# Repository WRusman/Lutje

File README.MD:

Open-source Battlebot ELRS receiver with built-in ESC's' for 2 brushed driving motors, 1 brushed weapon motor and 2 PWM outputs for external ESC.

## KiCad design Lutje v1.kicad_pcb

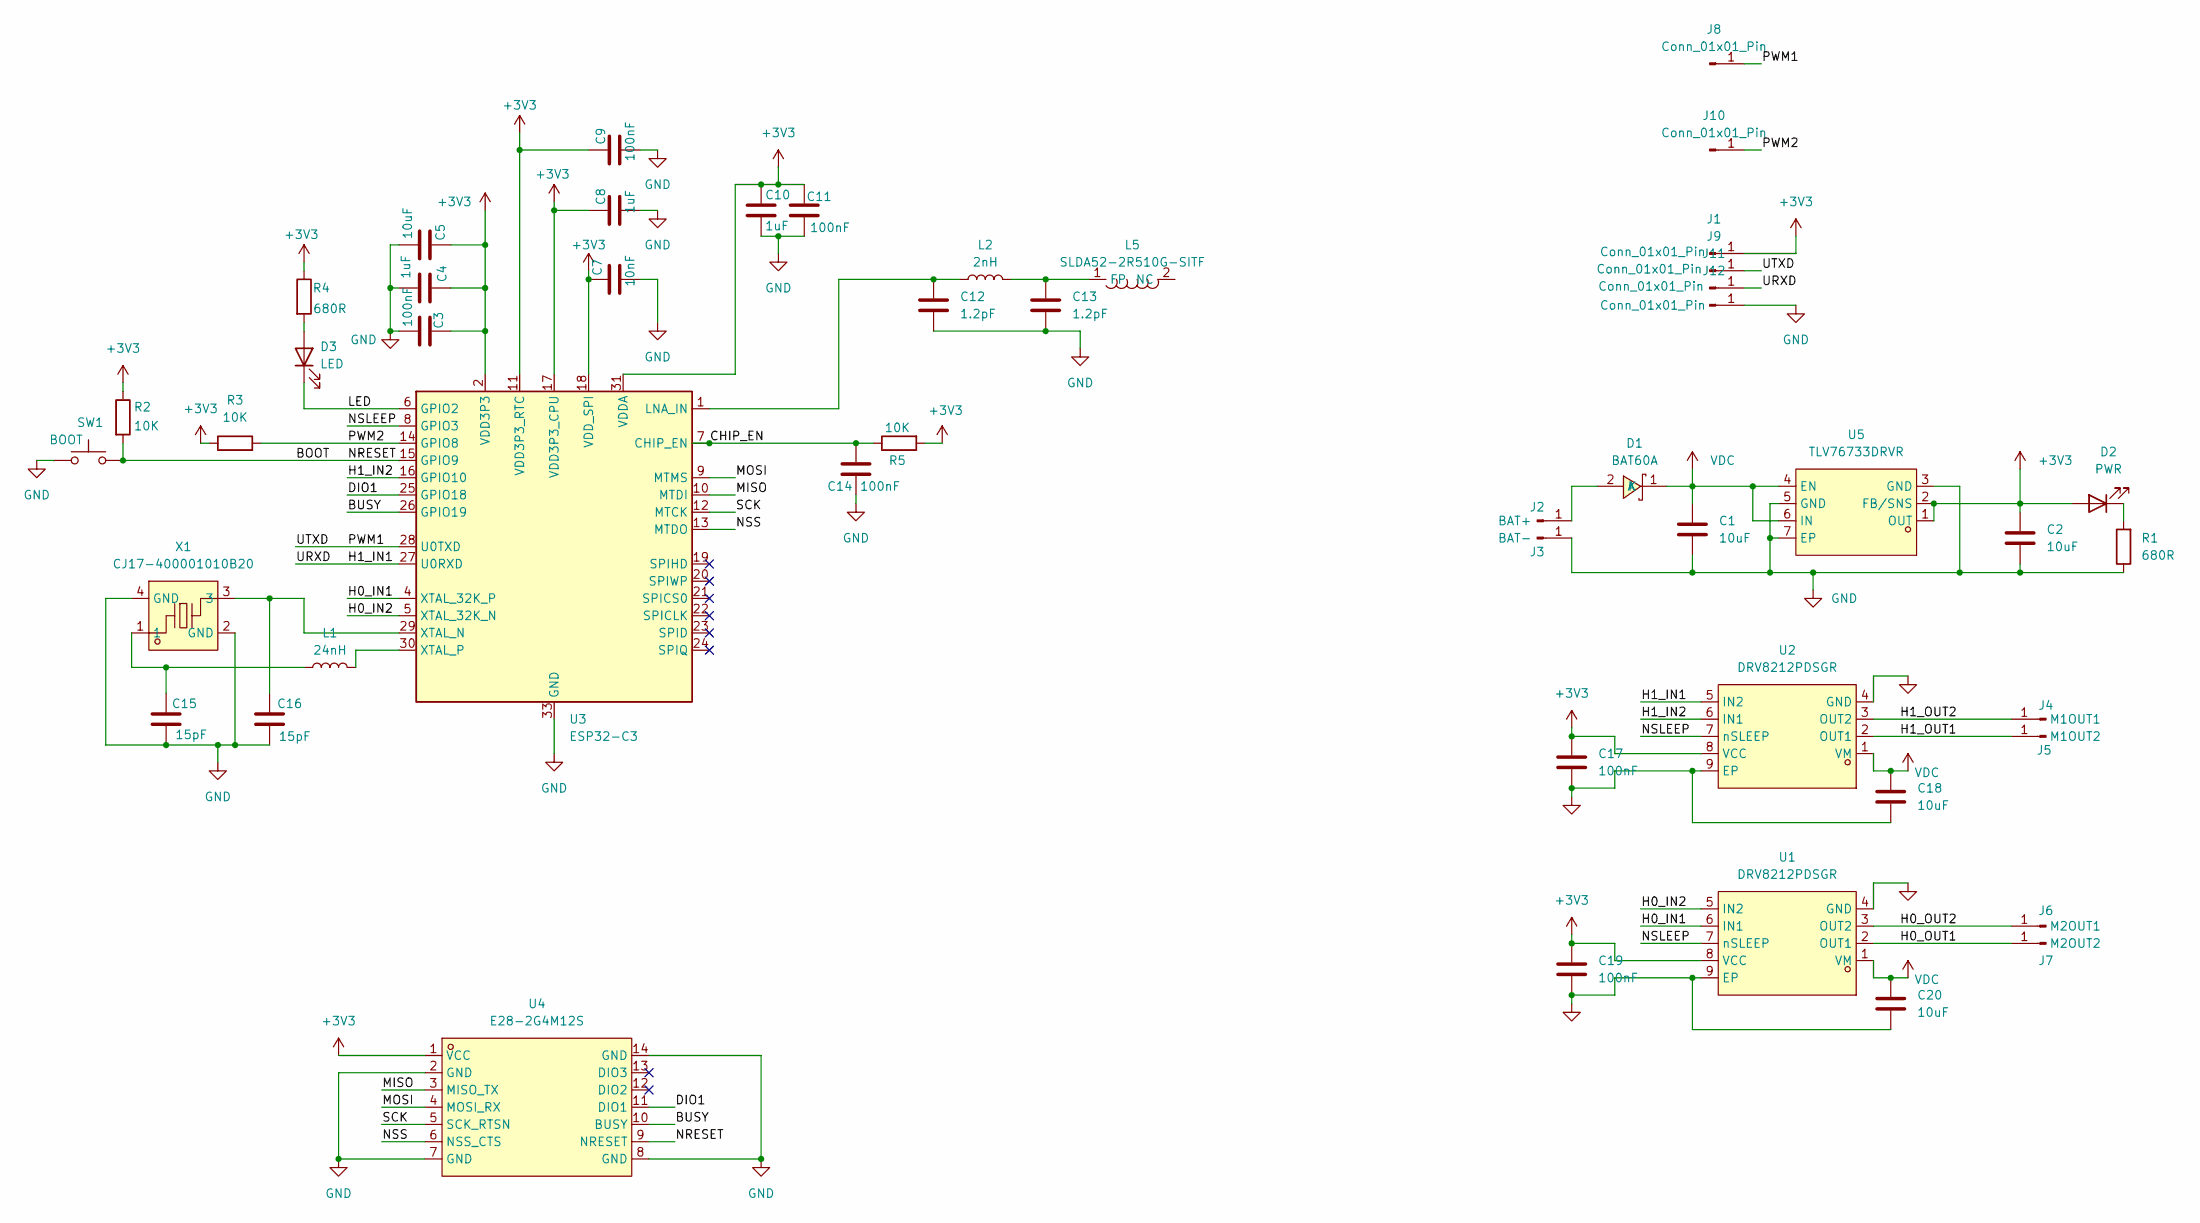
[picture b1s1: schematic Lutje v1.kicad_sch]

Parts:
C1, C2, C5, C18, C20: 10uF; C_0201_0603Metric; LCSC C96446
C3, C9, C11, C14, C17, C19: 100nF; C_0201_0603Metric; LCSC C14663
C4, C8, C10: 1uF; C_0201_0603Metric; LCSC C15849
C7: 10nF; C_0201_0603Metric; LCSC C57112
C12, C13: 1.2pF; C_0201_0603Metric; LCSC C1638
C15, C16: 15pF; C_0201_0603Metric; LCSC C1644
D1: BAT60A; SOD-323_L1.8-W1.3-LS2.5-RD; MPN BAT60A; LCSC Part C5355496
D2: PWR; LED_0201_0603Metric; LCSC C2286
D3: LED; LED_0201_0603Metric; LCSC C2286
J1, J9, J11, J12: Conn_01x01_Pin; SolderWirePad_1x01_SMD_1x2mm
J2: BAT+; SolderWirePad_1x01_SMD_1.5x3mm
J3: BAT-; SolderWirePad_1x01_SMD_1.5x3mm
J4: M1OUT1; SolderWirePad_1x01_SMD_1.5x3mm
J5: M1OUT2; SolderWirePad_1x01_SMD_1.5x3mm
J6: M2OUT1; SolderWirePad_1x01_SMD_1.5x3mm
J7: M2OUT2; SolderWirePad_1x01_SMD_1.5x3mm
J8, J10: Conn_01x01_Pin; SolderWirePad_1x01_SMD_1.5x3mm
L1: 24nH; L_0201_0603Metric; LCSC C74305
L2: 2nH; L_0201_0603Metric; LCSC C1028
L5: SLDA52-2R510G-SITF; ANT-SMD_L5.2-W2.1; MPN SLDA52-2R510G-S1TF; LCSC Part C96745
R1, R4: 680R; R_0201_0603Metric; LCSC C23228
R2, R3, R5: 10K; R_0201_0603Metric; LCSC C25804
SW1: BOOT; SW_Push_SPST_NO_Alps_SKRK; LCSC Part C202388
U1, U2: DRV8212PDSGR; WSON-8_L2.0-W2.0-P0.50-TL-EP; MPN DRV8212PDSGR; LCSC Part C5208051
U3: ESP32-C3; QFN-32-1EP_5x5mm_P0.5mm_EP3.7x3.7mm; LCSC Part C2858491
U4: E28-2G4M12S; WIRELM-SMD_E28-2G4M12S; MPN E28-2G4M12S; LCSC Part C411310
U5: TLV76733DRVR; WSON-6_L2.0-W2.0-P0.65-TL-EP; MPN TLV76733DRVR; LCSC Part C2848334
X1: CJ17-400001010B20; CRYSTAL-SMD_4P-L1.6-W1.2-BL; MPN CJ17-400001010B20; LCSC Part C2875272

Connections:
+3V3: C2.1, C3.2, C4.2, C5.2, C7.1, C8.1, C9.1, C10.1, C11.1, C17.1, C19.1, D2.2 (A), J1.1 (Pin_1_1), R2.1, R3.1, R4.1, R5.2, U1.8 (VCC), U2.8 (VCC), U3.2 (VDD3P3), U3.3 (VDD3P3), U3.11 (VDD3P3_RTC), U3.17 (VDD3P3_CPU), U3.18 (VDD_SPI), U3.31 (VDDA), U3.32 (VDDA), U4.1 (VCC), U5.1 (OUT), U5.2 (FB/SNS)
/BOOT: R2.2, SW1.2, U3.15 (GPIO9), U4.9 (NRESET)
/BUSY: U3.26 (GPIO19), U4.10 (BUSY)
/CHIP_EN: C14.1, R5.1, U3.7 (CHIP_EN)
/DIO1: U3.25 (GPIO18), U4.11 (DIO1)
/H0_IN1: U1.6 (IN1), U3.4 (XTAL_32K_P)
/H0_IN2: U1.5 (IN2), U3.5 (XTAL_32K_N)
/H0_OUT1: J7.1 (Pin_1_1), U1.2 (OUT1)
/H0_OUT2: J6.1 (Pin_1_1), U1.3 (OUT2)
/H1_IN1: J11.1 (Pin_1_1), U2.5 (IN2), U3.27 (U0RXD)
/H1_IN2: U2.6 (IN1), U3.16 (GPIO10)
/H1_OUT1: J5.1 (Pin_1_1), U2.2 (OUT1)
/H1_OUT2: J4.1 (Pin_1_1), U2.3 (OUT2)
/LED: D3.1 (K), U3.6 (GPIO2)
/MISO: U3.10 (MTDI), U4.3 (MISO_TX)
/MOSI: U3.9 (MTMS), U4.4 (MOSI_RX)
/NSLEEP: U1.7 (nSLEEP), U2.7 (nSLEEP), U3.8 (GPIO3)
/NSS: U3.13 (MTDO), U4.6 (NSS_CTS)
/PWM1: J8.1 (Pin_1_1), J9.1 (Pin_1_1), U3.28 (U0TXD)
/PWM2: J10.1 (Pin_1_1), R3.2, U3.14 (GPIO8)
/SCK: U3.12 (MTCK), U4.5 (SCK_RTSN)
GND: C1.2, C2.2, C3.1, C4.1, C5.1, C7.2, C8.2, C9.2, C10.2, C11.2, C12.2, C13.2, C14.2, C15.2, C16.2, C17.2, C18.2, C19.2, C20.2, J3.1 (Pin_1_1), J12.1 (Pin_1_1), R1.1, SW1.1, U1.4 (GND), U1.9 (EP), U2.4 (GND), U2.9 (EP), U3.33 (GND), U4.2 (GND), U4.7 (GND), U4.8 (GND), U4.14 (GND), U5.3 (GND), U5.5 (GND), U5.7 (EP), X1.2 (GND), X1.4 (GND)
unnamed: C15.1, L1.1, X1.1
unnamed: D1.2 (A), J2.1 (Pin_1_1)
unnamed: D2.1 (K), R1.2
unnamed: D3.2 (A), R4.2
unnamed: C13.1, L2.2, L5.1 (FP_1)
unnamed: C12.1, L2.1, U3.1 (LNA_IN)
unnamed: C16.1, U3.29 (XTAL_N), X1.3
unnamed: L1.2, U3.30 (XTAL_P)
VDC: C1.1, C18.1, C20.1, D1.1 (K), U1.1 (VM), U2.1 (VM), U5.4 (EN), U5.6 (IN)

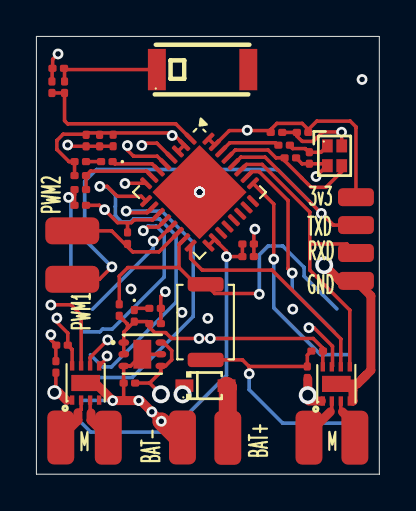
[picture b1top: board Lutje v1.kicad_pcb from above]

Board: 4 copper layers, 19.0 x 24.3 mm, 49 parts (1 on the bottom side), 31 nets.

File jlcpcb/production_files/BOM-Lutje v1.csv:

Comment,Designator,Footprint,LCSC,Quantity
1.2pF,"C12,C13",C_0201_0603Metric,C1638,2
100nF,"C11,C14,C17,C19,C3,C9",C_0201_0603Metric,C14663,6
10K,"R2,R3,R5",R_0201_0603Metric,C25804,3
10nF,C7,C_0201_0603Metric,C57112,1
10uF,"C1,C18,C2,C20,C5",C_0201_0603Metric,C96446,5
15pF,"C15,C16",C_0201_0603Metric,C1644,2
1uF,"C10,C4,C8",C_0201_0603Metric,C15849,3
24nH,L1,L_0201_0603Metric,C74305,1
2nH,L2,L_0201_0603Metric,C1028,1
680R,"R1,R4",R_0201_0603Metric,C23228,2
BAT60A,D1,SOD-323_L1.8-W1.3-LS2.5-RD,C5355496,1
BOOT,SW1,SW_Push_SPST_NO_Alps_SKRK,C202388,1
CJ17-400001010B20,X1,CRYSTAL-SMD_4P-L1.6-W1.2-BL,C2875272,1
DRV8212PDSGR,"U1,U2",WSON-8_L2.0-W2.0-P0.50-TL-EP,C5208051,2
ESP32-C3,U3,QFN-32-1EP_5x5mm_P0.5mm_EP3.7x3.7mm,C2858491,1
LED,D3,LED_0201_0603Metric,C2286,1
PWR,D2,LED_0201_0603Metric,C2286,1
SLDA52-2R510G-SITF,L5,ANT-SMD_L5.2-W2.1,C96745,1
TLV76733DRVR,U5,WSON-6_L2.0-W2.0-P0.65-TL-EP,C2848334,1
M1OUT2,J5,SolderWirePad_1x01_SMD_1.5x3mm,,1
M2OUT1,J6,SolderWirePad_1x01_SMD_1.5x3mm,,1
M1OUT1,J4,SolderWirePad_1x01_SMD_1.5x3mm,,1
M2OUT2,J7,SolderWirePad_1x01_SMD_1.5x3mm,,1
Conn_01x01_Pin,J12,SolderWirePad_1x01_SMD_1x2mm,,1
Conn_01x01_Pin,J11,SolderWirePad_1x01_SMD_1x2mm,,1
Conn_01x01_Pin,J10,SolderWirePad_1x01_SMD_1.5x3mm,,1
Conn_01x01_Pin,J9,SolderWirePad_1x01_SMD_1x2mm,,1
Conn_01x01_Pin,J8,SolderWirePad_1x01_SMD_1.5x3mm,,1
BAT-,J3,SolderWirePad_1x01_SMD_1.5x3mm,,1
BAT+,J2,SolderWirePad_1x01_SMD_1.5x3mm,,1
Conn_01x01_Pin,J1,SolderWirePad_1x01_SMD_1x2mm,,1
